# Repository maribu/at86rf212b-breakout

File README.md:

AT86RF212B Breakout
===================

This Repository contains an AT86RF212B breakout board that uses the basic
application schematic given in Section 5.1 "Basic Application Schematic" on
page 11 of the AT86RF212B datasheet (02/2015), with two differences:

1. The optional clock output is omitted
2. The sub-gigahertz antenna circuit from the [AT86RF215-XPRO](https://static5.arrow.com/pdfs/2015/6/30/10/21/54/282/atm_/manual/251atreb215-xpro_design_documentation.pdf)
   is used instead, but without shielding

This board is intentionally pin compatible with the openlabs RPI 802.15.4
radio. But note that the AT86RF212B differs from the AT86RF233 used in the
openlabs RPI 802.15.4 radio not only in the frequency band, but also behaves
slightly different. Thus, a driver for the AT86RF233 will not work unmodified
for the AT86RF212B.

WARNING
=======

1. The PCB contains no shielding for the RF filter, which will result in lower
   sensitivity and higher noise in the transmitted signal compared to e.g. the
   AT86RF215-XPRO reference design.
2. It is highly recommended to not order PCBs based on this design as of now.
   This design has never been tested.
3. The SMA connector for the antenna and the 2 x 6 pins 2.54 mm female pin
   header need to be hand soldered and are not part of the generated BOM.
4. There is absolutely no warranty.

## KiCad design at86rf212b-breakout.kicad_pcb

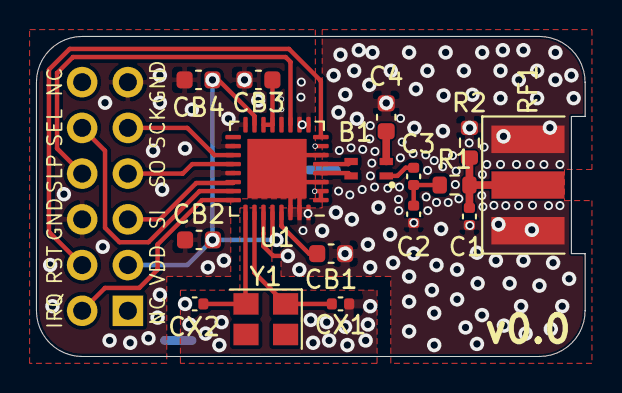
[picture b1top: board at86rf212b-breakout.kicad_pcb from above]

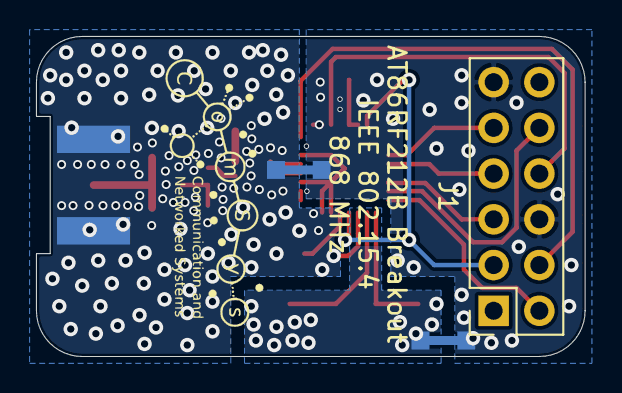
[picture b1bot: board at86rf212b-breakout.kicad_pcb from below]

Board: 2 copper layers, 30.5 x 17.8 mm, 19 parts (3 on the bottom side), 21 nets.

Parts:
B1: ATB2012-75011-T000
C1, C2: 2.2 pF; C_0402_1005Metric
C3: 15 pF; C_0402_1005Metric
C4: 8.2 pF; C_0603_1608Metric
CB1, CB2, CB3, CB4: 1 µF; C_0603_1608Metric
CX1, CX2: 12 pF; C_0402_1005Metric
J1: RPi Header; PinSocket_2x06_P2.54mm_Vertical
R1: 0 Ω; R_0603_1608Metric
R2: 10 kΩ; R_0603_1608Metric
R3, R4: 0 Ω; R0
RF1: Antenna; Connector-SMA
U1: AT86RF212B-ZU; QFN-32-1EP_5x5mm_P0.5mm_EP3.3x3.3mm
Y1: 16 MHz; Crystal_SMD_TXC_7M-4Pin_3.2x2.5mm

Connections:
/ANT: C1.1, R1.2, R2.1, RF1.1
/ANT': C2.1, C3.2, R1.1
/ANT'': B1.1, C3.1
/AVDD: CB1.2, U1.29
/Balun_GND: B1.2, C4.1
/DVDD: CB3.2, U1.13, U1.14
/IRQ: J1.2, U1.24
/MISO: J1.7, U1.20
/MOSI: J1.5, U1.22
/RFN: B1.3, U1.5
/RFP: B1.4, U1.4
/RST: J1.4, U1.8
/SCLK: J1.9, U1.19
/SEL: J1.10, U1.23
/SLP_TR: J1.8, U1.11
/XTAL1: CX1.2, U1.26, Y1.1
/XTAL2: CX2.2, U1.25, Y1.2
GND: CB2.1, CB3.1, CB4.1, J1.6, J1.11, R3.2, R4.2, U1.1, U1.2, U1.7, U1.9, U1.10, U1.12, U1.16, U1.18, U1.21
GND2: CX1.1, CX2.1, R3.1
GNDA: C1.2, C2.2, C4.2, CB1.1, R2.2, R4.1, RF1.2, U1.3, U1.6, U1.27, U1.30, U1.31, U1.32, U1.33
VDD: CB2.2, CB4.2, J1.3, U1.15, U1.28
